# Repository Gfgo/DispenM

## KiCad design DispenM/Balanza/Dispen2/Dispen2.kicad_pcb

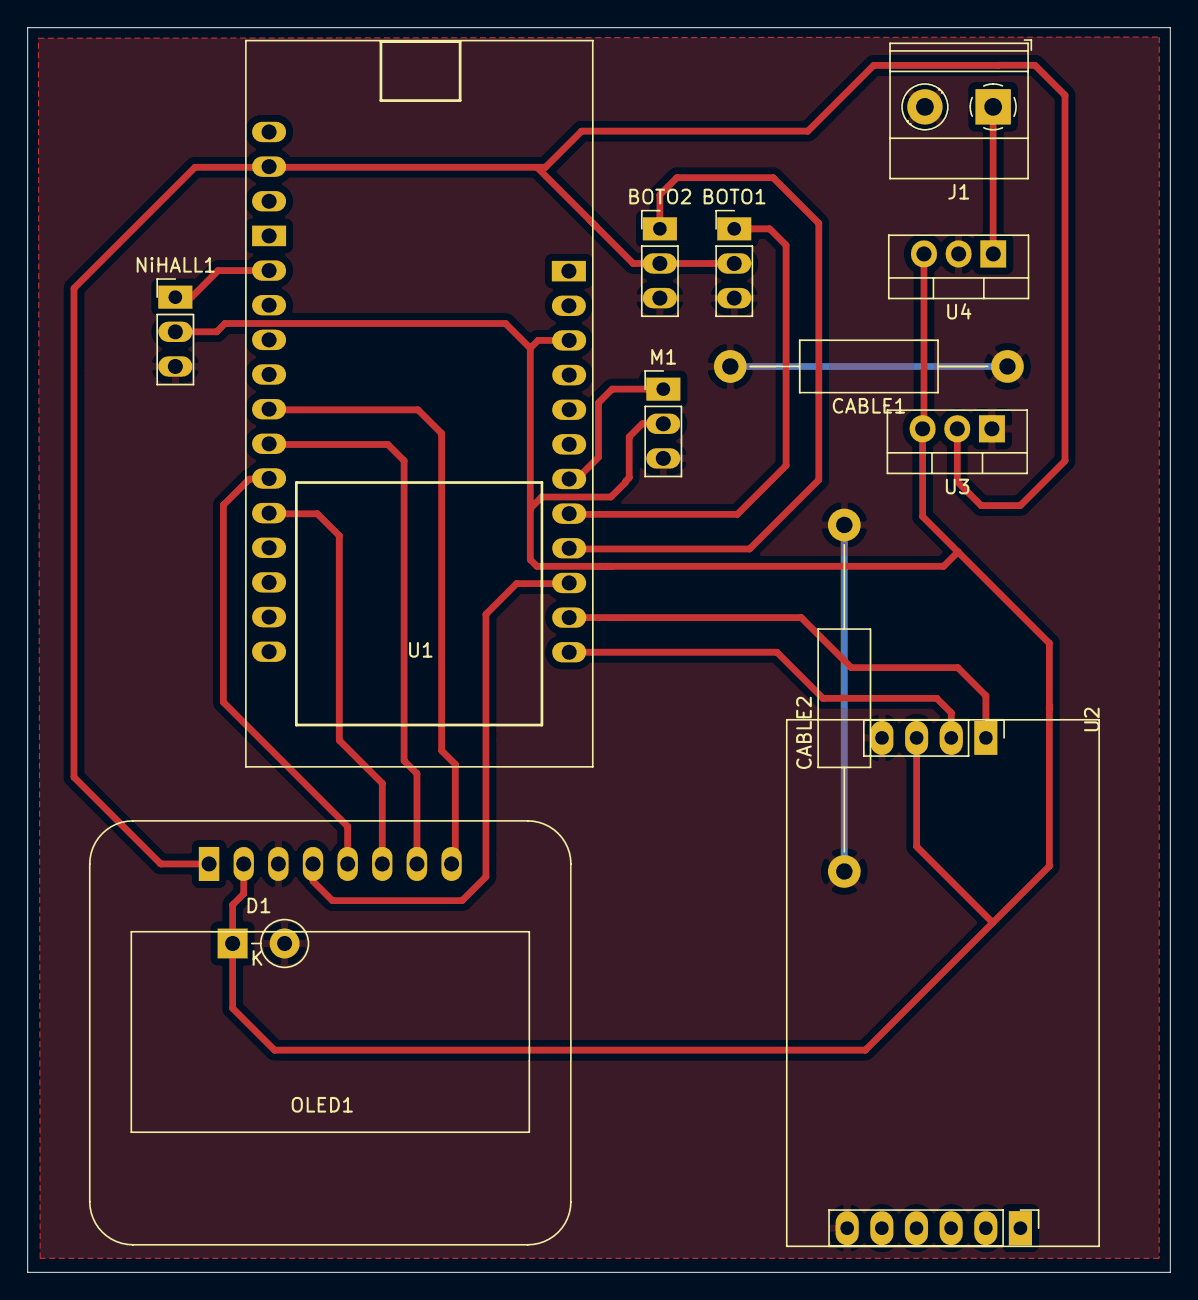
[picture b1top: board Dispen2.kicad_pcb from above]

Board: 2 copper layers, 83.8 x 91.2 mm, 13 parts (0 on the bottom side), 11 nets.

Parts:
BOTO1, BOTO2: Conn_01x03; PinHeader_1x03_P2.54mm_Vertical
CABLE1: R; R_Axial_DIN0411_L9.9mm_D3.6mm_P20.32mm_Horizontal
CABLE2: R; R_Axial_DIN0411_L9.9mm_D3.6mm_P25.40mm_Horizontal
D1: 1N4001; D_DO-41_SOD81_P3.81mm_Vertical_KathodeUp
J1: Conn_01x02; TerminalBlock_Phoenix_MKDS-1,5-2_1x02_P5.00mm_Horizontal
M1: Motor_Servo; PinHeader_1x03_P2.54mm_Vertical
NiHALL1: Conn_01x03; PinHeader_1x03_P2.54mm_Vertical
OLED1: Conn_01x08; OLED128X128
U1: LoRa32U4; Lora32U4
U2: DS3231MZ; DS3231MH
U3: LD1117S33TR_SOT223; TO-220-3_Vertical
U4: LM7805_TO220; TO-220-3_Vertical

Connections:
+3V3: BOTO1.2, BOTO2.2, OLED1.1, U3.2
+5V: D1.1, M1.2, NiHALL1.2, OLED1.2, U2.2, U3.3, U4.3
CS: OLED1.7, U1.23
DC: OLED1.8, U1.22
GND: BOTO1.3, BOTO2.3, CABLE1.1, CABLE1.2, CABLE2.1, CABLE2.2, D1.2, J1.2, M1.3, NiHALL1.3, OLED1.3, U2.5, U3.1, U4.2
unnamed: J1.1, U4.1
unnamed: NiHALL1.1, U1.18
SCK: OLED1.5, U1.15
SCL: U1.3, U2.8
SDA: U1.2, U2.7
SI: OLED1.6, U1.16

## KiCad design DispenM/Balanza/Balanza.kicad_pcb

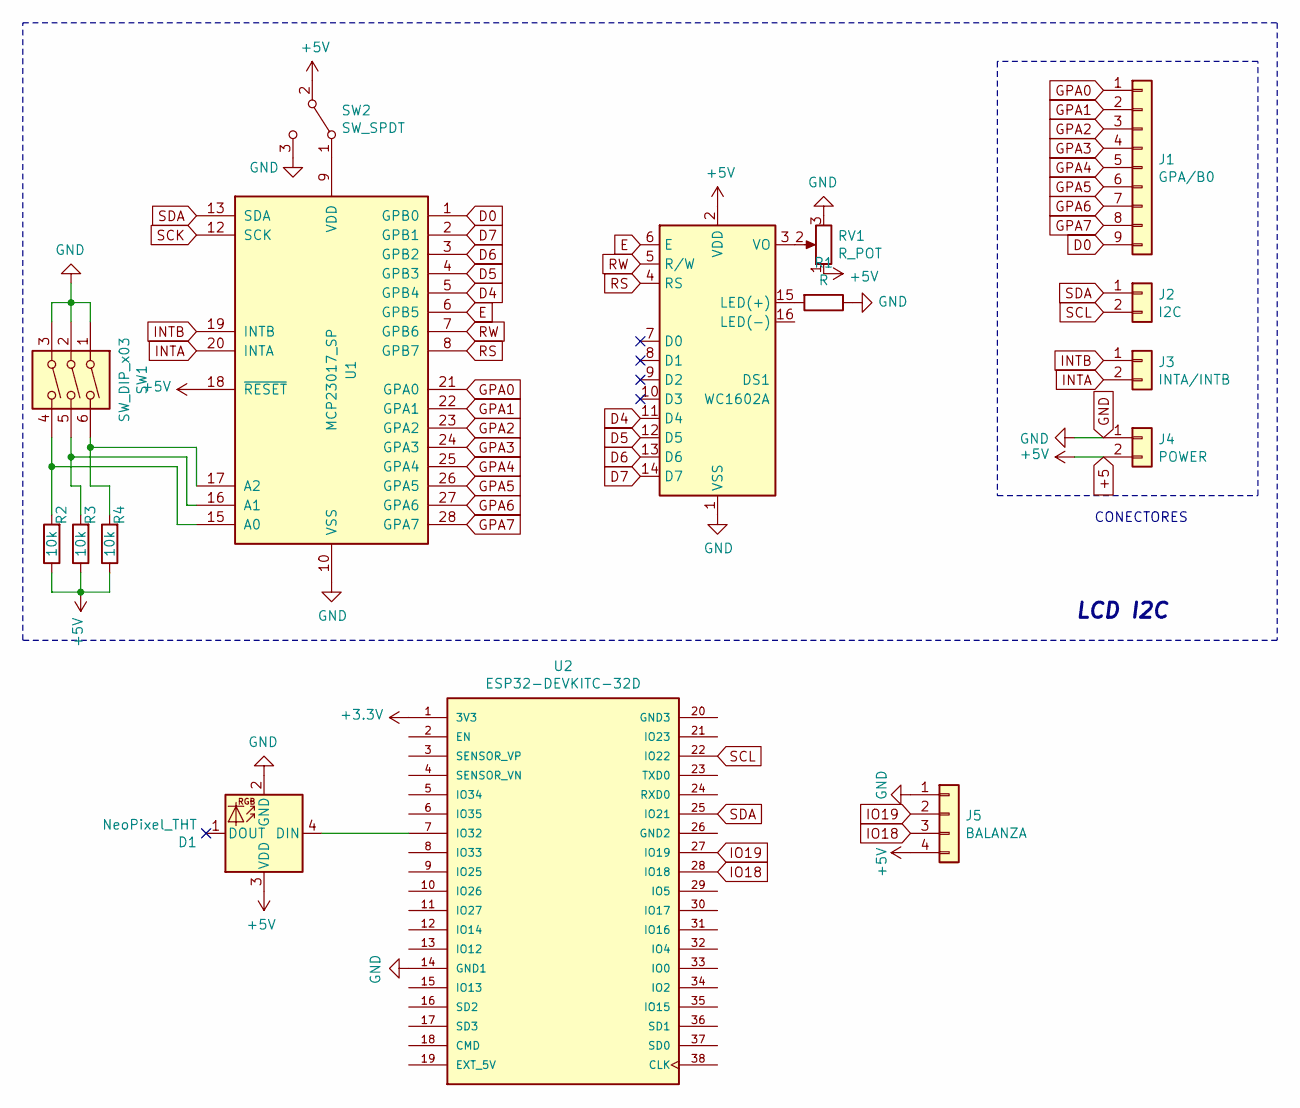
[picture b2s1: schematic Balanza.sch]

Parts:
D1: NeoPixel_THT; PinHeader_1x04_P2.54mm_Vertical
DS1: WC1602A
J1: GPA/B0; PinHeader_1x09_P2.54mm_Vertical
J2: I2C; PinHeader_1x02_P2.54mm_Vertical
J3: INTA/INTB; PinHeader_1x02_P2.54mm_Vertical
J4: POWER; PinHeader_1x02_P2.54mm_Vertical
J5: BALANZA; ModuloHX711
R1: R; R_Axial_DIN0207_L6.3mm_D2.5mm_P10.16mm_Horizontal
R2, R3, R4: 10k; R_Axial_DIN0207_L6.3mm_D2.5mm_P10.16mm_Horizontal
RV1: R_POT; Potentiometer_ACP_CA9-V10_Vertical
SW1: SW_DIP_x03; SW_DIP_SPSTx03_Slide_9.78x9.8mm_W7.62mm_P2.54mm
SW2: SW_SPDT; Slide_Switch_SPDT_ThroughHole
U1: MCP23017_SP; DIP-28_W7.62mm
U2: ESP32-DEVKITC-32D; Esp32wroverD; PARTREV 4

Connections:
+3V3: U2.1 (3V3)
+5: D1.3 (VDD), DS1.2 (VDD), J4.2, J5.4, R2.1, R3.1, R4.1, RV1.1, SW2.2 (B), U1.18 (~RESET~)
D0: J1.9, U1.1 (GPB0)
D4: DS1.11 (D4), U1.5 (GPB4)
D5: DS1.12 (D5), U1.4 (GPB3)
D6: DS1.13 (D6), U1.3 (GPB2)
D7: DS1.14 (D7), U1.2 (GPB1)
E: DS1.6 (E), U1.6 (GPB5)
GND: D1.2 (GND), DS1.1 (VSS), J4.1, J5.1, R1.1, RV1.3, SW1.1, SW1.2, SW1.3, SW2.3 (C), U1.10 (VSS), U2.14 (GND1)
GPA0: J1.1, U1.21 (GPA0)
GPA1: J1.2, U1.22 (GPA1)
GPA2: J1.3, U1.23 (GPA2)
GPA3: J1.4, U1.24 (GPA3)
GPA4: J1.5, U1.25 (GPA4)
GPA5: J1.6, U1.26 (GPA5)
GPA6: J1.7, U1.27 (GPA6)
GPA7: J1.8, U1.28 (GPA7)
INTA: J3.2, U1.20 (INTA)
INTB: J3.1, U1.19 (INTB)
IO18: J5.3, U2.28 (IO18)
IO19: J5.2, U2.27 (IO19)
unnamed: D1.4 (DIN), U2.7 (IO32)
unnamed: DS1.3 (VO), RV1.2
unnamed: DS1.15 (LED(+)), R1.2
unnamed: R2.2, SW1.4, U1.15 (A0)
unnamed: R3.2, SW1.5, U1.16 (A1)
unnamed: R4.2, SW1.6, U1.17 (A2)
unnamed: SW2.1 (A), U1.9 (VDD)
RS: DS1.4 (RS), U1.8 (GPB7)
RW: DS1.5 (R/W), U1.7 (GPB6)
SCK: U1.12 (SCK)
SCL: J2.2, U2.22 (IO22)
SDA: J2.1, U1.13 (SDA), U2.25 (IO21)

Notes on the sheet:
CONECTORES
LCD I2C

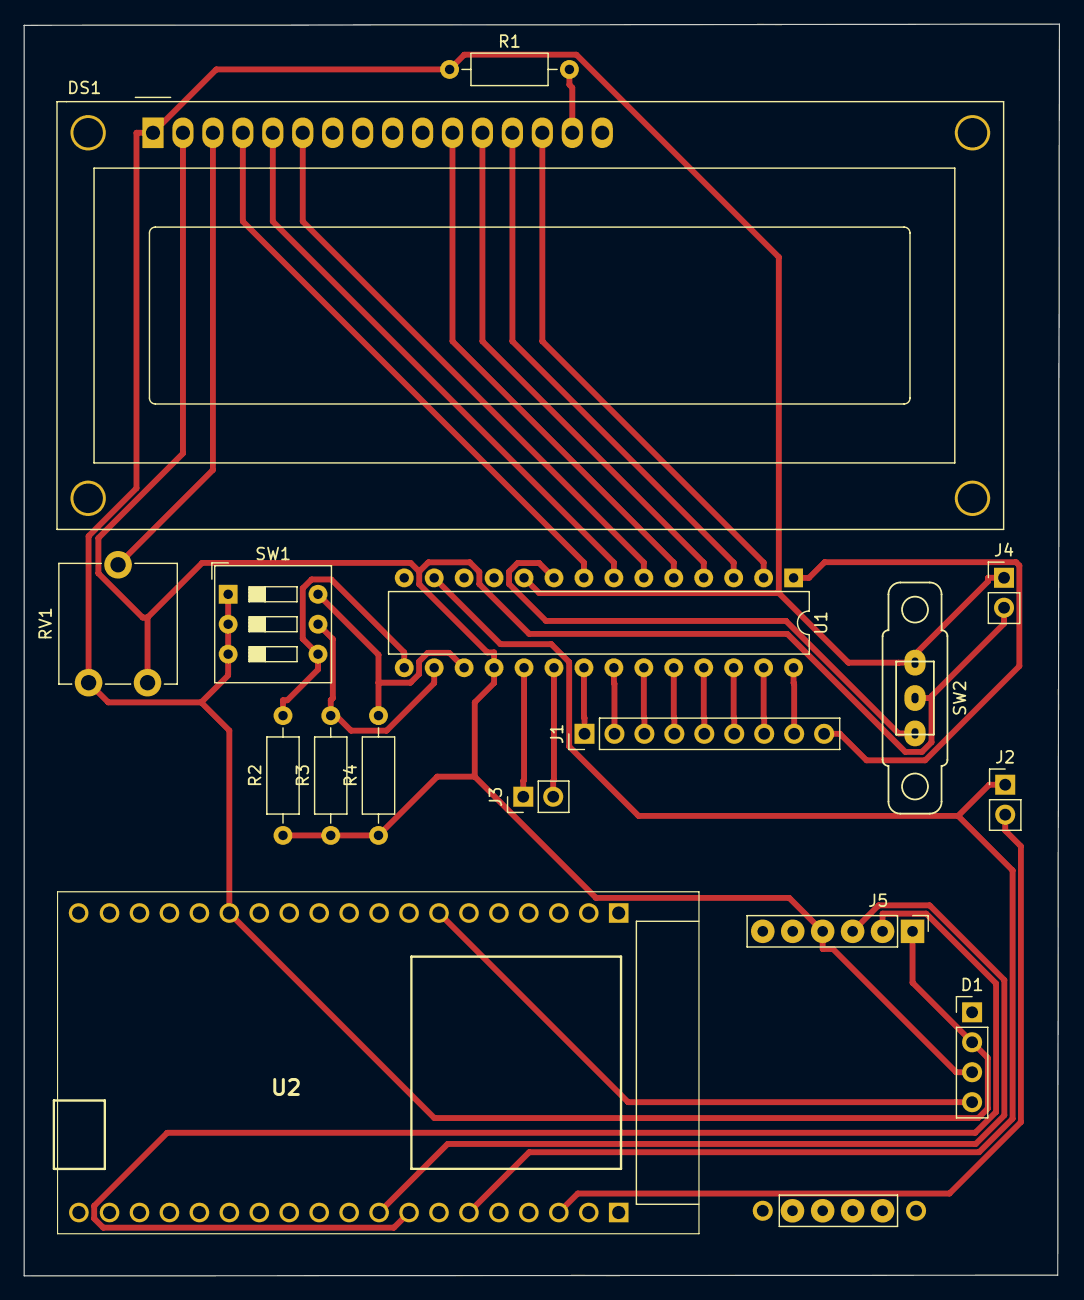
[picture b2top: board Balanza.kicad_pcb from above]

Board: 2 copper layers, 87.8 x 106.2 mm, 16 parts (0 on the bottom side), 31 nets.

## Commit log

2021-11-12 Inicio ble y motores
2021-11-16 Inclusion de lcd no funca
2021-11-19 Actualización programa
2021-11-22 Arreglos de codigo
2021-11-23 Inclusion de balanza no sirven luces
2021-11-24 Led funciona con errores
2021-11-25 LCD y luces funcionando faltan motores
2021-11-30 Se mejora velocidad quitando lectura de promedio
2021-12-02 Update a esp32
2021-12-07 Todo ok BLE por arduino.
2022-08-02 Update DispenM.ino
    Programación con bluetooth incluido.
2022-11-08 Circuito
2023-06-20 Nuevo programa
2023-07-14 Actualización
2023-07-19 Correccion de plano
2023-07-24 Actualizacion software y pcb
2023-07-25 Correccion pcb
2023-07-26 PCB actualizada
2023-09-12 Cambio de fuente
2023-10-09 Ok sensor Hu
2023-11-08 nuevo circuito
    nuevo circuito
2024-05-22 actualización 22/05
2024-07-05 pantalla y reloj interfaz ok2024
    pantalla y reloj interfaz ok2024
2024-07-09 actualizacion 90/07/2024
    botones servo y hall ok
2024-11-27 27/11/2024
    Actualizacion circuito
